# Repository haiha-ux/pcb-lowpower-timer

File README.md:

# Low-power battery timer (2×AA, soft-latch power button, STM32L0, 2-layer)

A 50 × 40 mm timer board that runs from two AA cells. One button turns it on; the firmware keeps itself powered
through a HOLD pin and turns itself off on a long press. When it is off, the battery sees only leakage, about 0.5 µA
typical. The board has a 32.768 kHz RTC, a magnetic buzzer, two LEDs and a switched battery-voltage divider. It is
a 2-layer board, and every part has an LCSC number for JLCPCB assembly.

| Top | Bottom |
|---|---|
|  |  |

Some parts render without bodies because their footprints have no 3D model.

## Files

| Path | What |
|---|---|
| `lowpower_timer.kicad_pro` / `.kicad_sch` / `.kicad_pcb` | the project (one A3 schematic sheet) |
| `lowpower_timer.pretty/` | project footprint for the Huaneng MLT-8530 buzzer |
| `docs/lowpower_timer_schematic.pdf` | schematic as PDF |
| `fab/gerber_jlcpcb.zip` | Gerber X2 (copper, mask, silk, paste, outline) and Excellon drill, PTH and NPTH |
| `fab/BOM_JLCPCB.csv`, `fab/CPL_JLCPCB.csv` | JLC BOM (Comment, Designator, Footprint, LCSC Part #) and placement file |
| `design/nets.json` | the intended connection of every pin, written by hand |
| `design/lowpower_timer.net`, `design/erc.json`, `reports/drc.json` | netlist, ERC and DRC reports from kicad-cli |
| `reports/route.dsn`, `reports/route.ses` | the Freerouting input and the routing result this board was built from |
| `tools/build_pcb.py` | builds the board from the netlist: placement, Freerouting, GND pours and stitching, silkscreen |
| `tools/export_fab.py` | writes `fab/`, the renders and the schematic PDF |
| `tools/check_netlist.py` | compares the netlist with `design/nets.json` pin by pin |
| `tools/cpl_rotations_db.csv`, `tools/cpl_rotations_local.csv` | CPL rotation corrections (see "Assembly") |

## Design

### Battery and reverse polarity
- Two AA cells in an external holder, on a JST-PH 2-pin connector (J1, pin 1 = +, marked on the silkscreen).
  A 2×AA holder is about 58 × 31 mm and would not fit a ≤ 50 × 40 mm board; a wired holder also lets the board sit
  in a lid.
- Q1, a DMG2305UX P-MOSFET, sits in the + lead (drain to the battery, source to VIN), with its gate to GND through
  R1 100 kΩ.
  - Cells the right way round: the body diode conducts first, then VGS = −VBAT turns the channel on. At end of life
    (VBAT = 1.8 V) VGS is −1.8 V, where RDS(on) is at most 200 mΩ, and VGS(th) is −0.5 to −0.9 V (DMG2305UX
    datasheet p.2). At about 200 mA input that is a 40 mV drop.
  - Cells reversed: the body diode is reverse-biased and VGS ≈ 0, so nothing conducts.
  - No series diode: a Schottky would cost 0.2–0.3 V of the 1.8 V left at end of life.

### 3.3 V boost
- U1 TPS61099 (adjustable, WSON-6 2 × 2 mm). It runs from 0.7 V input (datasheet p.5) and starts at 0.7 V with a
  light load (p.12).
- **Input above the output.** Two lithium AA cells reach 3.6 V, above 3.3 V. The TPS61099 handles that in Down mode:
  "In Down mode, the output voltage can still be regulated at target value even when input voltage is higher than
  the output voltage" (p.1). It only changes to Pass-Through, where VOUT follows VIN, when VIN > VOUT + 0.5 V (p.1),
  which is about 3.9 V here. So the output stays regulated for every AA chemistry; no buck-boost is needed.
- **Load disconnect is the reason for this part.** "In shutdown mode, the device stops switching and the rectifying
  PMOS fully turns off, providing the completed disconnection between input and output" (p.11; "True disconnection
  during shutdown", p.1). An ordinary boost lets VIN through the inductor and diode to VOUT while it is off, which
  would keep the MCU half-powered. The TPS61097A-33 was rejected because it does the opposite and connects the
  battery to the load in shutdown (its datasheet p.1).
- **Output voltage.** The 3.3 V-fixed TPS610994 is only sold on LCSC as a DSBGA, so the adjustable part sets the
  output with R2 + R3 (2 MΩ + 300 kΩ) over R4 (1 MΩ).
  - VOUT = VREF × (1 + 2.3 MΩ / 1 MΩ). VREF is 1.00 V in PWM (heavier loads) but 1.03 V in PFM at light load
    (datasheet p.5), so VOUT is 3.30 V when the buzzer runs and about **3.40 V while the board sleeps**.
  - Both are inside the STM32L031's 1.65–3.6 V range. The firmware must not assume a 3.3 V ADC reference: measure
    VDDA with the internal VREFINT channel before converting the battery reading.
  - The divider draws about 1 µA. TI suggests 100× the FB leakage for best accuracy (p.15); that holds against the
    10 nA typical leakage but not against the 50 nA maximum, which can push VOUT about 1 % high. Nothing on the
    board cares.
- L1 2.2 µH (Würth 74404024022, one of TI's listed parts; 2.2 µH is the recommended value for VOUT > 3 V, p.14).
  CIN 10 µF, COUT 2 × 10 µF (p.6: COUT 10 µF minimum, 20 µF nominal). The 0603 10 V X5R parts lose capacitance at
  3.4 V; at about 60 % retained, COUT is still ≈ 12 µF.

### Soft-latch power button
```
VIN ─SW1─┬─ BTN ──D1a──┐
         │             ├── EN (U1) ── R6 2M ── GND
         R5 1M  HOLD ──D1b┘   (D1 = BAT54C, common cathode)
         │      (PA1)
        GND   BTN ── R7 100k ── PA3 (button sense)
```
- **Press:** SW1 pulls BTN to VIN, D1a lifts EN, and the boost starts. The MCU boots and drives HOLD (PA1) high,
  which keeps EN high through D1b after the button is released.
- **Off:** the firmware sees a long press on PA3, **waits until the button is released**, and only then drives HOLD
  low. Dropping HOLD while the button is still held does nothing (EN stays high through D1a), and the board would
  come straight back on when the firmware rebooted.
- **EN at the lowest battery voltage:** pressing at VBAT = 1.8 V gives EN ≈ 1.8 V − 0.1 V (BAT54 at about 1 µA) =
  1.7 V. VIH is 1.2 V for VIN > 1.5 V, and 0.8 × VIN below that (datasheet p.6).
- **EN low when released:** the leakage current into the EN pin, IEN_LKG, is 50 nA max at VEN = 5 V (datasheet
  p.6; the FB pin has a separate 50 nA figure). Through R6 2 MΩ that is 0.1 V, under VIL = 0.4 V.
  - A 10 MΩ pull-down would have saved 1.3 µA in sleep, but in the worst case it could leave EN at 0.5 V, so it was
    not used.
- **Button sense:** PA3 is an FT (5 V-tolerant) pin (DS10668 Table 15 p.40), so BTN at 3.2–3.6 V is safe on it, and
  R7 limits the current if the MCU is unpowered during a press.
- **Diode leakage:** when the board is off, every node of the latch sits at 0 V, so the diodes carry no reverse
  current. When it is on, D1a is reverse-biased by about 3.3 V; BAT54C reverse current at 3 V is about 0.1 µA at
  25 °C and about 3 µA at 75 °C (Diodes BAT54 datasheet ds11005, Fig. 2 p.3, read off the curve). That counts in
  the sleep budget only.

### MCU and RTC
- U2 STM32L031F6P6 (TSSOP-20). I chose it over the ATtiny1616 for two reasons.
  - Stop mode with the RTC on the 32.768 kHz crystal draws about 0.55 µA at 3 V (DS10668 Fig. 18 p.63; the feature
    list on p.1 says 0.6 µA). The ATtiny1616's equivalent figure is 0.69 µA (DS40002204A Table 36-5 p.508).
  - The ATtiny's 32k oscillator wants CL 7.5–12.5 pF with ESR at most 40–80 kΩ (Table 36-14 p.512), and the common
    Epson crystal's 70 kΩ typical ESR sits at that edge.
  - SWD also gives breakpoint debugging.
- **Pin use:**

| Function | Pin |
|---|---|
| HOLD | PA1 (7) |
| Button sense | PA3 (9), FT |
| VBAT ADC | PA4 (10), ADC_IN4 |
| Battery-sense enable | PA5 (11) |
| Buzzer PWM | PA6 (12), TIM22_CH1, FT |
| LEDs | PA7 (13) / PB1 (14) |
| SWD | PA13 (19) / PA14 (20) |
| Unused, left open | PA0, PA2, PA9, PA10 |

  - BOOT0 is pulled to GND by R8 10 kΩ, and NRST has 100 nF to GND.
- **Crystal:** Y1 Epson FC-135, 32.768 kHz, CL = 7 pF; C0 1.0 pF typ, ESR 70 kΩ typ (FC-135 specification p.2).
  - Oscillator margin, after ST AN2867: gm_crit = 4 · ESR · (2π f)² · (C0 + CL)² = 4 · 70 kΩ · (2π · 32768 Hz)² ·
    (8 pF)² = 0.76 µA/V.
  - The L031's LSE "medium high" drive is rated for crystals up to 1.7 µA/V (DS10668 Table 40 p.71), so the
    firmware selects LSEDRV = 10, with 2.2× headroom.
  - The 12.5 pF version of the same crystal (JLC Basic) would need 2.16 µA/V, which only the highest drive level
    (2.7 µA/V) covers. That is 25 % headroom at typical ESR, and the crystal has no maximum ESR listed.
- **Load capacitors:** CL = C9·C10/(C9 + C10) + Cstray. With Cstray ≈ 3.5 pF (pin plus trace; an assumption, ST
  suggests 2–7 pF), C9 = C10 = 2 × (7 − 3.5) = 7 pF; 6.8 pF C0G is used. Trim with the RTC calibration register if
  needed.

### Battery voltage measurement
- Q3 (AO3401A) is a high-side switch in front of the R11/R12 100 kΩ / 100 kΩ divider. Q4 (2N7002) pulls Q3's gate
  down only while PA5 is high. R9 holds Q3 off and R10 holds Q4 off when the MCU is unpowered or in reset.
- Off, the divider draws nothing. Because it is cut off at the top, VBAT never reaches PA4 through it while the MCU
  is unpowered; a low-side switch would leave PA4 at VBAT through R11 and leak into the pin's protection diode.
- PA4 sees at most 1.8 V. C11 100 nF holds the node for the ADC sample.

### Buzzer and LEDs
- BZ1 Huaneng MLT-8530 magnetic buzzer: 2.7 kHz, 16 Ω coil, 95 mA max at 5 Vp-p (specification p.2).
  - It is driven exactly as its specification p.3 shows: NPN with a 470 Ω base resistor and a 1N4148 across the coil
    (Q5 MMBT3904, D2 1N4148W).
  - R14 100 kΩ keeps Q5 off while PA6 floats during reset.
- The footprint (`lowpower_timer.pretty`) uses the pad size and position of the official EasyEDA footprint for
  LCSC C94599 (2.4 mm square pads at ±3.6 mm). Pad 1 (+) is top-left and pad 2 (−) bottom-left, from the maker's
  outline drawing (specification p.2). The datasheet itself gives no land pattern.
- D3/D4 are red 0603 LEDs with 1 kΩ (≈ 1.3 mA each); red is the only JLC Basic 0603 LED.

### Programming
- SWD goes through a Tag-Connect TC2030-NL footprint (J2: 1 VCC, 2 SWDIO, 3 NRST, 4 SWCLK, 5 GND), which has no part
  to buy.
- J2's VCC is the 3.3 V rail, and with the board off that rail is disconnected from the battery. There are two ways
  to program:
  - **Power from the probe:** let the debugger supply 3.3 V into J2 pin 1. The TPS61099's true disconnect (p.1,
    p.11) keeps that from flowing back into the battery side.
  - **Power from the battery:** hold SW1 down for the whole programming session, or flash firmware that raises HOLD
    early.
- A blank MCU leaves PA1 floating, so on a first power-up from the battery the board stays on only while the button
  is held.

## Layout

- 2 layers, 1.6 mm, 50 × 40 mm, four M2 holes 2.5 mm in from the corners. Both layers have a GND pour, tied together
  by a grid of stitching vias (about 70) placed wherever one clears every other net.
- The boost sits at the top: L1 and the input capacitor next to the VIN/SW pins, the output capacitors and the FB
  divider next to the VOUT/FB pins. That keeps the switching loop short, away from the crystal.
- The crystal and its load capacitors sit right at PC14/PC15, with the VDDA, VDD and NRST capacitors on the same
  side of the MCU. The battery connector is on the left edge, and the button and LEDs on the bottom edge.
- Routing was done by Freerouting 2.5.0 from `reports/route.dsn`. `tools/build_pcb.py autoroute` repeats the run
  until the board, with its pours, has no unconnected item, and the SES that produced this board is kept in
  `reports/`.

Design rules (JLC 2-layer capability is 0.1/0.1 mm track/space, 0.3 mm via drill):

| Rule | Value |
|---|---|
| Clearance | 0.15 mm |
| Signal tracks | 0.2 mm |
| VIN / switch node / buzzer | 0.4 mm (still enters the 0.65 mm pitch WSON pads) |
| Battery input | 0.5 mm |
| Vias | 0.6/0.3 mm |
| Copper to edge | 0.3 mm |

Rebuild:
```
python tools/check_netlist.py design/lowpower_timer.net design/nets.json
"C:/Program Files/KiCad/10.0/bin/python.exe" tools/build_pcb.py place dsn autoroute silk
python tools/export_fab.py
```

## Current budget

### OFF (battery connected, boost disabled), VBAT 2.4–3.2 V

| Item | Typical | Datasheet maximum | Source |
|---|---|---|---|
| TPS61099 shutdown current into VIN | 0.5 µA | 1.6 µA (VIN 3.7 V) | TPS61099 datasheet p.5 |
| Q3 AO3401A off (IDSS) | not given | 1 µA (VDS −30 V) | AO3401A datasheet p.2 |
| Q4 2N7002 off (IDSS), through R9 | not given | 80 nA (VDS 60 V) | JSCJ 2N7002 datasheet (LCSC C8545) p.2 |
| Q1 gate leakage through R1 (VGS ≈ −VBAT) | not given | 100 nA (VGS ±8 V) | DMG2305UX datasheet p.2 |
| Button network, D1, R5, R6, R7 | 0 (all nodes at 0 V) | 0 | by construction |
| MCU, divider, buzzer, LEDs | 0 (VOUT disconnected) | 0 | TPS61099 p.11 |
| **Total** | **≈ 0.5 µA** | **≈ 2.8 µA** | |

The ≤ 1 µA target is met at typical values. The guaranteed maxima are specified at 8–60 V and 3.7 V, so they
overstate the worst case at 3.2 V, but no datasheet bounds it lower. Nothing has been measured.

### Sleep (on, MCU in Stop with RTC, HOLD high, everything else off), from the 3.4 V rail

| Item | Current | Source |
|---|---|---|
| STM32L031 Stop + RTC (LSE) | ≈ 0.55 µA | DS10668 Fig. 18 p.63 (measured with LSE low drive; medium-high drive adds an unquantified amount) |
| FB divider R2+R3+R4 | 1.03 µA | 3.4 V / 3.3 MΩ |
| EN pull-down R6 (EN ≈ 3.3 V) | 1.65 µA | 3.3 V / 2 MΩ |
| D1a reverse leakage (≈ 3.3 V) | 0.1 µA at 25 °C, ≈ 3 µA at 75 °C | Diodes ds11005 Fig. 2 p.3 |
| TPS61099 IQ from VOUT | 0.6 µA | TPS61099 datasheet p.5 |
| **Total on 3.4 V** | **≈ 3.9 µA** at 25 °C | |

From the battery at VIN 2.4 V: TPS61099 IQ from VIN is 0.4 µA (p.5). The efficiency curve gives 83 % at a 10 µA load
(VIN 2.5 V, VOUT 3.3 V, Fig. 6-5 p.7) and falls further at 4 µA; with an assumed 70 %, the battery current is
0.4 + 3.9 × 3.4 / (2.4 × 0.70) ≈ **8.3 µA**.

### Alarm (buzzer sounding, MCU running at 1 MHz, alarm LED on)

| Item | Current | Source |
|---|---|---|
| Buzzer, 2.7 kHz 50 % square wave | ≤ 95 mA (rated maximum at 5 Vp-p; lower at 3.3 V, not measured) | MLT-8530 spec p.2 |
| MCU Run, 1 MHz, Range 3 | 140 µA | DS10668 Table 24 p.57 |
| LED D4 | 1.3 mA | (3.3 − 2.0) V / 1 kΩ |
| **Total on 3.3 V** | **≤ 97 mA** | |

From the battery at 2.4 V and 93.6 % efficiency at 50 mA (Fig. 6-5 p.7, the nearest point read):
97 × 3.3 / (2.4 × 0.936) ≈ **143 mA** at most.

### Battery life with 2000 mAh AA cells

Example: always on, sleeping, with a 1 ms wake every second at 140 µA (+0.14 µA average) and 30 s of alarm per day.

| Part | Per day |
|---|---|
| Sleep, 8.4 µA × 24 h | 0.20 mAh |
| Alarm, 143 mA × 30 s | 1.19 mAh |
| **Total** | **≈ 1.4 mAh/day** |

- With 80 % of 2000 mAh usable, that is about 1150 days, **roughly 3 years**.
- At 140 mA an alkaline AA delivers noticeably less than its rated capacity, so the alarm share is optimistic.
- Switched OFF at 0.5 µA, the cells' own self-discharge (a few % per year) is larger than the board's draw.

## Assembly (JLCPCB)

- Upload `fab/gerber_jlcpcb.zip`: 2 layers, 1.6 mm.
- Assembly is top side only, with `fab/BOM_JLCPCB.csv` and `fab/CPL_JLCPCB.csv`. The mounting holes and the
  Tag-Connect pads are left out because there is nothing to place.
- **Rotations:** the CPL applies JLCKicadTools' correction table (`tools/cpl_rotations_db.csv`, copied unchanged
  from github.com/matthewlai/JLCKicadTools, GPL-3.0) plus `tools/cpl_rotations_local.csv`; the longest matching
  pattern wins.
  - Corrections applied: J1 +180°; SOT-23 parts (Q1, Q3, Q4, Q5, D1) −90°; U2 (TSSOP-20) +270°; U1 (WSON-6) +270°.
  - U1's 270° is a local entry: the upstream table has none for WSON-6, but gives 270/−90 to every other SON package
    it lists (VSON-8, USON-10, TDSON-8, WSON-8). That makes it the most likely value, not a confirmed one.
  - No entry exists for Y1, L1, BZ1 or the passives, so those go at 0°.
  - **Check every part in JLC's placement preview before paying**, especially U1, Y1 and BZ1. BZ1 is polarised:
    its + lead must land on pad 1 (top-left).
- Extended parts (one loading fee each): TPS61099, STM32L031, DMG2305UX, the 7 pF crystal, L1, the buzzer and the
  JST connector. Everything else is Basic or Preferred.

## Checks done (on this version)

- `kicad-cli sch erc` (10.0.8): 0 errors, 0 warnings (`design/erc.json`).
- `tools/check_netlist.py`: all 29 named nets match `design/nets.json` pin for pin, and every other pin is declared
  no-connect. On its first run it caught a real schematic short (LED2 to GND, from overlapping label stubs).
- `kicad-cli pcb drc --severity-all --schematic-parity --refill-zones` (10.0.8): **0 errors, 0 warnings, 0
  unconnected items, 0 schematic parity issues** (`reports/drc.json`).
- An independent review of the schematic led to these README corrections: Down mode and the Pass-Through
  threshold, VOUT 3.4 V in PFM and VREFINT in firmware, the power-off sequence, how to program a board that is off,
  the buzzer footprint against the EasyEDA footprint, and the 2N7002 / DMG2305UX leakage figures.

## Not checked

- Nothing has been built or measured: OFF current, sleep current, soft-latch timing, crystal start-up, buzzer
  current at 3.3 V.
- The buzzer polarity on the footprint comes from the maker's drawing. The EasyEDA footprint numbers its pads
  differently, and I did not see which of its pads it assigns to +.
- Efficiency below 10 µA load is an assumption (70 %); the datasheet curve stops at 10 µA.
- CPL rotations for U1 (inferred) and for parts with no correction-table entry (see "Assembly").
- No firmware is included; the power-off sequence and the VREFINT correction above are requirements for it.

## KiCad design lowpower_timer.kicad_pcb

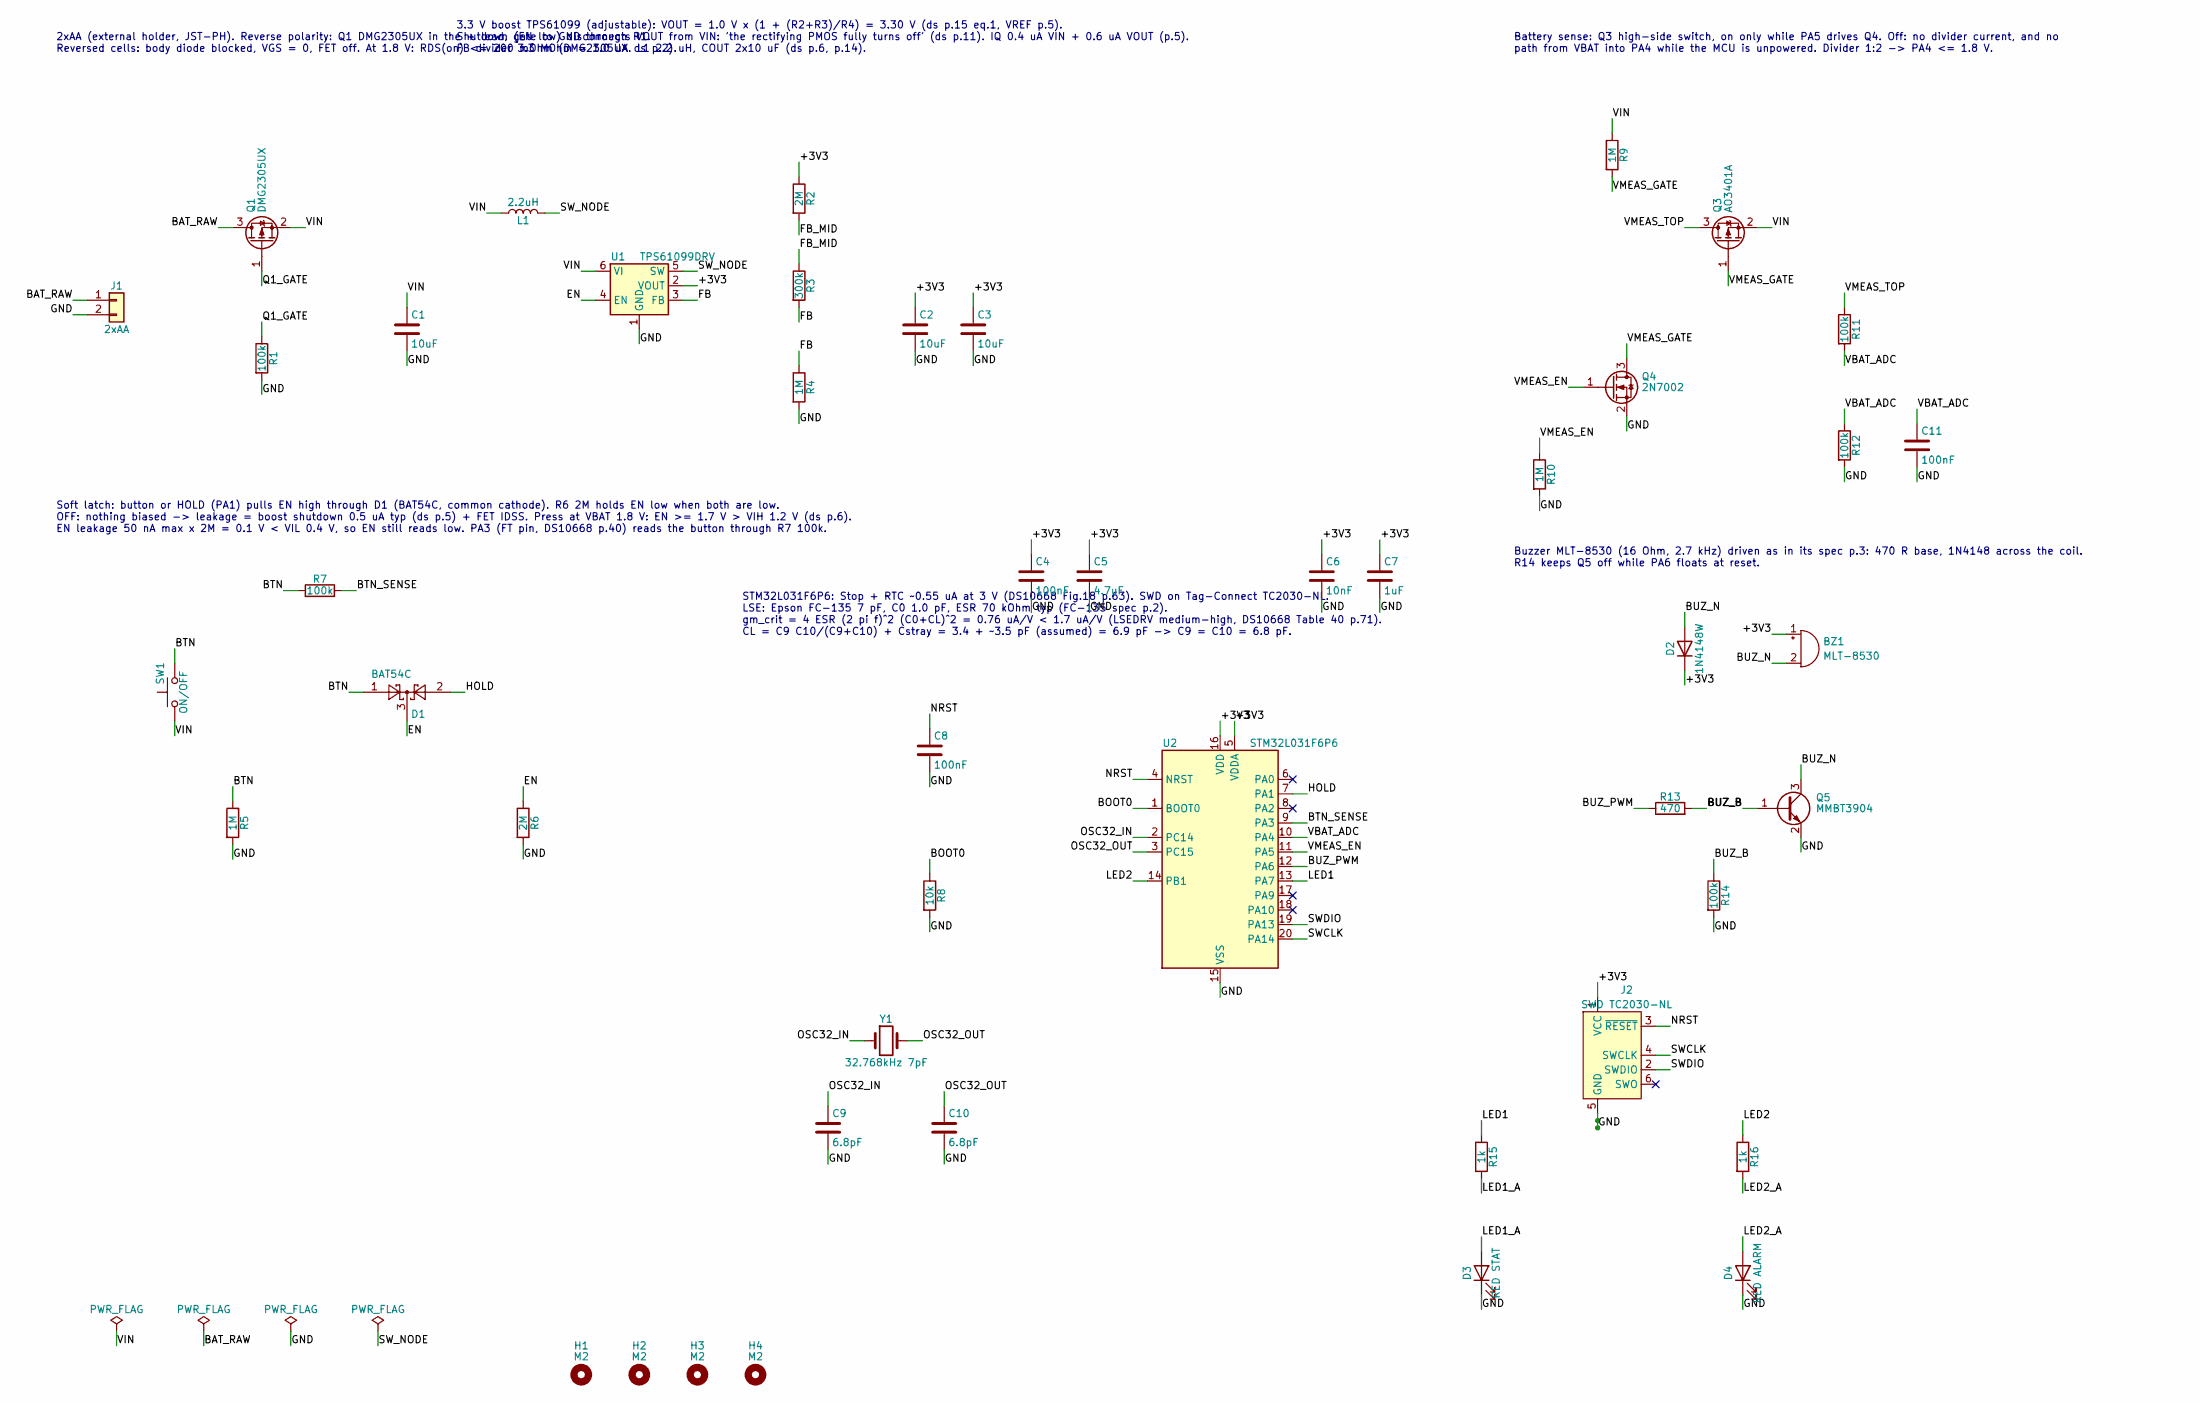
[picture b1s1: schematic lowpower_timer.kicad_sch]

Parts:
BZ1: MLT-8530; Buzzer_Huaneng_MLT-8530; MPN MLT-8530; JLC Extended
C1, C2, C3: 10uF; C_0603_1608Metric; MPN CL10A106KP8NNNC; JLC Basic
C4, C8, C11: 100nF; C_0402_1005Metric; MPN CL05B104KO5NNNC; JLC Basic
C5: 4.7uF; C_0603_1608Metric; MPN CL10A475KO8NNNC; JLC Basic
C6: 10nF; C_0402_1005Metric; MPN CL05B103KB5NNNC; JLC Basic
C7: 1uF; C_0402_1005Metric; MPN CL05A105KA5NQNC; JLC Basic
C9, C10: 6.8pF; C_0402_1005Metric; MPN 0402CG6R8C500NT; JLC Preferred
D1: BAT54C; SOT-23; MPN BAT54C; JLC Preferred
D2: 1N4148W; D_SOD-123; MPN 1N4148W; JLC Basic
D3: RED STAT; LED_0603_1608Metric; MPN KT-0603R; JLC Basic
D4: RED ALARM; LED_0603_1608Metric; MPN KT-0603R; JLC Basic
H1, H2, H3, H4: M2; MountingHole_2.2mm_M2
J1: 2xAA; JST_PH_S2B-PH-SM4-TB_1x02-1MP_P2.00mm_Horizontal; MPN S2B-PH-SM4-TB(LF)(SN); JLC Extended
J2: SWD TC2030-NL; Tag-Connect_TC2030-IDC-NL_2x03_P1.27mm_Vertical
L1: 2.2uH; L_1008_2520Metric; MPN 74404024022; JLC Extended
Q1: DMG2305UX; SOT-23; MPN DMG2305UX-7; JLC Extended
Q3: AO3401A; SOT-23; MPN AO3401A; JLC Basic
Q4: 2N7002; SOT-23; MPN 2N7002; JLC Basic
Q5: MMBT3904; SOT-23; MPN MMBT3904(RANGE:100-300); JLC Basic
R1, R7, R11, R12, R14: 100k; R_0402_1005Metric; MPN 0402WGF1003TCE; JLC Basic
R2, R6: 2M; R_0603_1608Metric; MPN 0603WAF2004T5E; JLC Basic
R3: 300k; R_0603_1608Metric; MPN 0603WAF3003T5E; JLC Basic
R4: 1M; R_0603_1608Metric; MPN 0603WAF1004T5E; JLC Basic
R5, R9, R10: 1M; R_0402_1005Metric; MPN 0402WGF1004TCE; JLC Basic
R8: 10k; R_0402_1005Metric; MPN 0402WGF1002TCE; JLC Basic
R13: 470; R_0402_1005Metric; MPN 0402WGF4700TCE; JLC Basic
R15, R16: 1k; R_0402_1005Metric; MPN 0402WGF1001TCE; JLC Basic
SW1: ON/OFF; SW_Push_1P1T_XKB_TS-1187A; MPN TS-1187A-B-A-B; JLC Basic
U1: TPS61099DRV; WSON-6-1EP_2x2mm_P0.65mm_EP1x1.6mm; MPN TPS61099DRVR; JLC Extended
U2: STM32L031F6P6; TSSOP-20_4.4x6.5mm_P0.65mm; MPN STM32L031F6P6; JLC Extended
Y1: 32.768kHz 7pF; Crystal_SMD_3215-2Pin_3.2x1.5mm; MPN Q13FC13500002; JLC Extended

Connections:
/+3V3: BZ1.1 (+), C2.1, C3.1, C4.1, C5.1, C6.1, C7.1, D2.1 (K), J2.1 (VCC), R2.1, U1.2 (VOUT), U2.5 (VDDA), U2.16 (VDD)
/BAT_RAW: J1.1, Q1.3 (D)
/BOOT0: R8.1, U2.1 (BOOT0)
/BTN: D1.1, R5.1, R7.1, SW1.2
/BTN_SENSE: R7.2, U2.9 (PA3)
/BUZ_B: Q5.1 (B), R13.2, R14.1
/BUZ_N: BZ1.2 (-), D2.2 (A), Q5.3 (C)
/BUZ_PWM: R13.1, U2.12 (PA6)
/EN: D1.3, R6.1, U1.4 (EN)
/FB: R3.2, R4.1, U1.3 (FB)
/FB_MID: R2.2, R3.1
/GND: C1.2, C2.2, C3.2, C4.2, C5.2, C6.2, C7.2, C8.2, C9.2, C10.2, C11.2, D3.1 (K), D4.1 (K), J1.2, J2.5 (GND), Q4.2 (S), Q5.2 (E), R1.2, R4.2, R5.2, R6.2, R8.2, R10.2, R12.2, R14.2, U1.1 (GND), U1.7 (GND), U2.15 (VSS)
/HOLD: D1.2, U2.7 (PA1)
/LED1: R15.1, U2.13 (PA7)
/LED1_A: D3.2 (A), R15.2
/LED2: R16.1, U2.14 (PB1)
/LED2_A: D4.2 (A), R16.2
/NRST: C8.1, J2.3 (~RESET), U2.4 (NRST)
/OSC32_IN: C9.1, U2.2 (PC14), Y1.1
/OSC32_OUT: C10.1, U2.3 (PC15), Y1.2
/Q1_GATE: Q1.1 (G), R1.1
/SWCLK: J2.4 (SWCLK), U2.20 (PA14)
/SWDIO: J2.2 (SWDIO), U2.19 (PA13)
/SW_NODE: L1.2, U1.5 (SW)
/VBAT_ADC: C11.1, R11.2, R12.1, U2.10 (PA4)
/VIN: C1.1, L1.1, Q1.2 (S), Q3.2 (S), R9.1, SW1.1, U1.6 (VI)
/VMEAS_EN: Q4.1 (G), R10.1, U2.11 (PA5)
/VMEAS_GATE: Q3.1 (G), Q4.3 (D), R9.2
/VMEAS_TOP: Q3.3 (D), R11.1

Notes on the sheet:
2xAA (external holder, JST-PH). Reverse polarity: Q1 DMG2305UX in the + lead, gate to GND through R1. Reversed cells: body diode blocked, VGS = 0, FET off. At 1.8 V: RDS(on) <= 200 mOhm (DMG2305UX ds p.2).
3.3 V boost TPS61099 (adjustable): VOUT = 1.0 V x (1 + (R2+R3)/R4) = 3.30 V (ds p.15 eq.1, VREF p.5). Shutdown (EN low) disconnects VOUT from VIN: 'the rectifying PMOS fully turns off' (ds p.11). IQ 0.4 uA VIN + 0.6 uA VOUT (p.5). FB divider 3.3 MOhm = 1.0 uA. L1 2.2 uH, COUT 2x10 uF (ds p.6, p.14).
Soft latch: button or HOLD (PA1) pulls EN high through D1 (BAT54C, common cathode). R6 2M holds EN low when both are low. OFF: nothing biased -> leakage = boost shutdown 0.5 uA typ (ds p.5) + FET IDSS. Press at VBAT 1.8 V: EN >= 1.7 V > VIH 1.2 V (ds p.6). EN leakage 50 nA max x 2M = 0.1 V < VIL 0.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
STM32L031F6P6: Stop + RTC ~0.55 uA at 3 V (DS10668 Fig.18 p.63). SWD on Tag-Connect TC2030-NL. LSE: Epson FC-135 7 pF, C0 1.0 pF, ESR 70 kOhm typ (FC-135 spec p.2). gm_crit = 4 ESR (2 pi f)^2 (C0+CL)^2 = 0.76 uA/V < 1.7 uA/V (LSEDRV medium-high, DS10668 Table 40 p.71). CL = C9 C10/(C9+C10) + Cstray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
Battery sense: Q3 high-side switch, on only while PA5 drives Q4. Off: no divider current, and no path from VBAT into PA4 while the MCU is unpowered. Divider 1:2 -> PA4 <= 1.8 V.
Buzzer MLT-8530 (16 Ohm, 2.7 kHz) driven as in its spec p.3: 470 R base, 1N4148 across the coil. R14 keeps Q5 off while PA6 floats at reset.

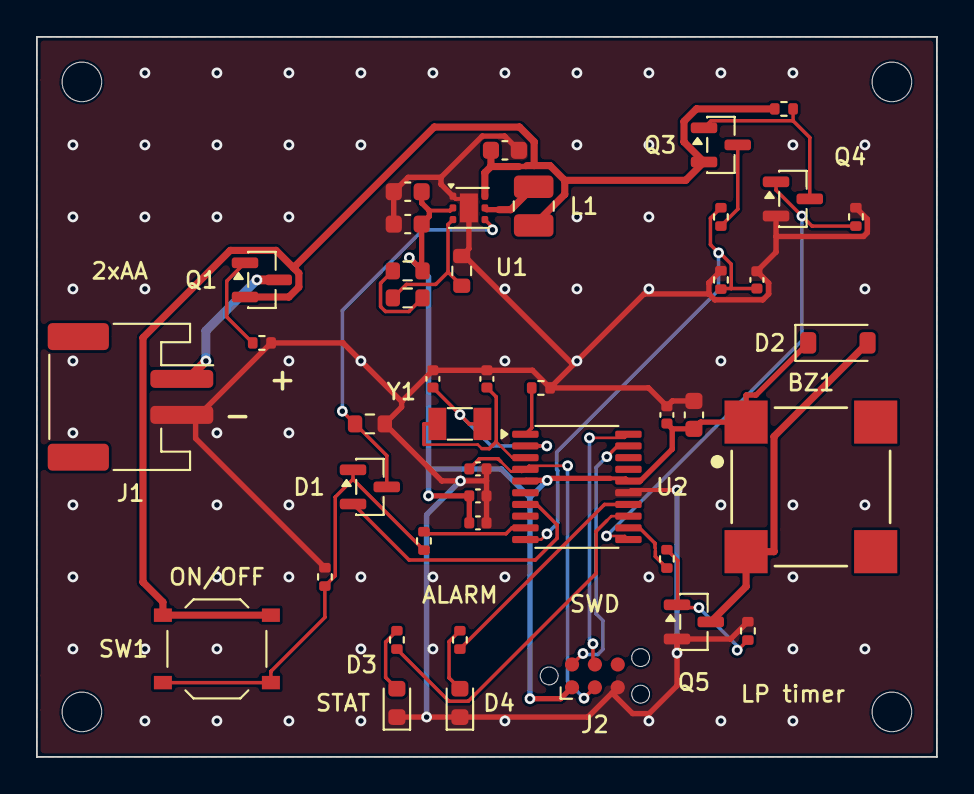
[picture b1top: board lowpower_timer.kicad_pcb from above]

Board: 2 copper layers, 50.0 x 40.0 mm, 47 parts (0 on the bottom side), 29 nets.

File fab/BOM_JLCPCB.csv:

Comment,Designator,Footprint,LCSC Part #
MLT-8530,BZ1,Buzzer_Huaneng_MLT-8530,C94599
10uF,C1-C3,C_0603_1608Metric,C19702
100nF,"C4,C8,C11",C_0402_1005Metric,C1525
4.7uF,C5,C_0603_1608Metric,C19666
10nF,C6,C_0402_1005Metric,C15195
1uF,C7,C_0402_1005Metric,C52923
6.8pF,"C9,C10",C_0402_1005Metric,C1576
BAT54C,D1,SOT-23,C22466350
1N4148W,D2,D_SOD-123,C81598
RED STAT,D3,LED_0603_1608Metric,C2286
RED ALARM,D4,LED_0603_1608Metric,C2286
2xAA,J1,JST_PH_S2B-PH-SM4-TB_1x02-1MP_P2.00mm_Horizontal,C295747
2.2uH,L1,L_1008_2520Metric,C2046874
DMG2305UX,Q1,SOT-23,C150470
AO3401A,Q3,SOT-23,C15127
2N7002,Q4,SOT-23,C8545
MMBT3904,Q5,SOT-23,C20526
100k,"R1,R7,R11,R12,R14",R_0402_1005Metric,C25741
2M,"R2,R6",R_0603_1608Metric,C22976
300k,R3,R_0603_1608Metric,C23024
1M,R4,R_0603_1608Metric,C22935
1M,"R5,R9,R10",R_0402_1005Metric,C26083
10k,R8,R_0402_1005Metric,C25744
470,R13,R_0402_1005Metric,C25117
1k,"R15,R16",R_0402_1005Metric,C11702
ON/OFF,SW1,SW_Push_1P1T_XKB_TS-1187A,C318884
TPS61099DRV,U1,WSON-6-1EP_2x2mm_P0.65mm_EP1x1.6mm,C2842395
STM32L031F6P6,U2,TSSOP-20_4.4x6.5mm_P0.65mm,C115208
32.768kHz 7pF,Y1,Crystal_SMD_3215-2Pin_3.2x1.5mm,C48615
